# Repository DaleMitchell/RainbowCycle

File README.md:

# RainbowCycle
My very first circuit board. I'm very proud to say that the first fabrication of it worked! :)

The PCB was fabricated by Seeedstudio: http://www.seeedstudio.com/service/

Components on the board were hand soldered by me.

## YouTube Video

## Bill of materials
* 10x Common Anode RGB LEDs - 5mm Square (Sometimes called 'Super flux' or 'Piranha') 
* 1x ATMega328P-PU - same chip used by the Arduino Uno
* 2x TLC5940s - 16 Channel LED Driver
* 2x 10K Ohm Potentiometers - adjustable speed and brightness
* 2x 2K Ohm Resistors - current limiting for LED drivers
* 2x 10K Ohm Resistors - pull-up resistors for the ICs
* 1x 100uF Capacitor - filtering capacitor for stable power to ICs
* 3x 0.1uF Capacitors - also filtering capacitors for each IC
* 1x 16MHz Crystal - clock input for ATMega328P-PU
* 2x 22pF Capacitors - used by the 16MHz crystal
* 1x Mini-USB Connector - for power only, doesn't program Arduino
* 1x ISP Header - for programming the ATMega328P-PU
* 1x Terminal Blocks 5.08mm - alternative connector for power
* 1x Diode - protection against reverse polarity on block terminal

## Things I'd do differently if I wanted to revise the board

* Use trimpots that are flush with the board instead of panel mount potentiometers. Even when soldered on both sides of the board, the currently used potentiometers bend easily.
* Replace ATMega328P-PU with a microcontroller that can be programmed directly through USB. ICSP was a hassle, and I couldn't find a through-hole means of converting USB to serial.
* Provide overvoltage protection, or at least put a warning on the silkscreen that the circuit is only rated for 5V.
* Make pads on some components slightly bigger for some components, like resistors and small capacitors.
* Use slightly higher clearance for ground plane (maybe?).

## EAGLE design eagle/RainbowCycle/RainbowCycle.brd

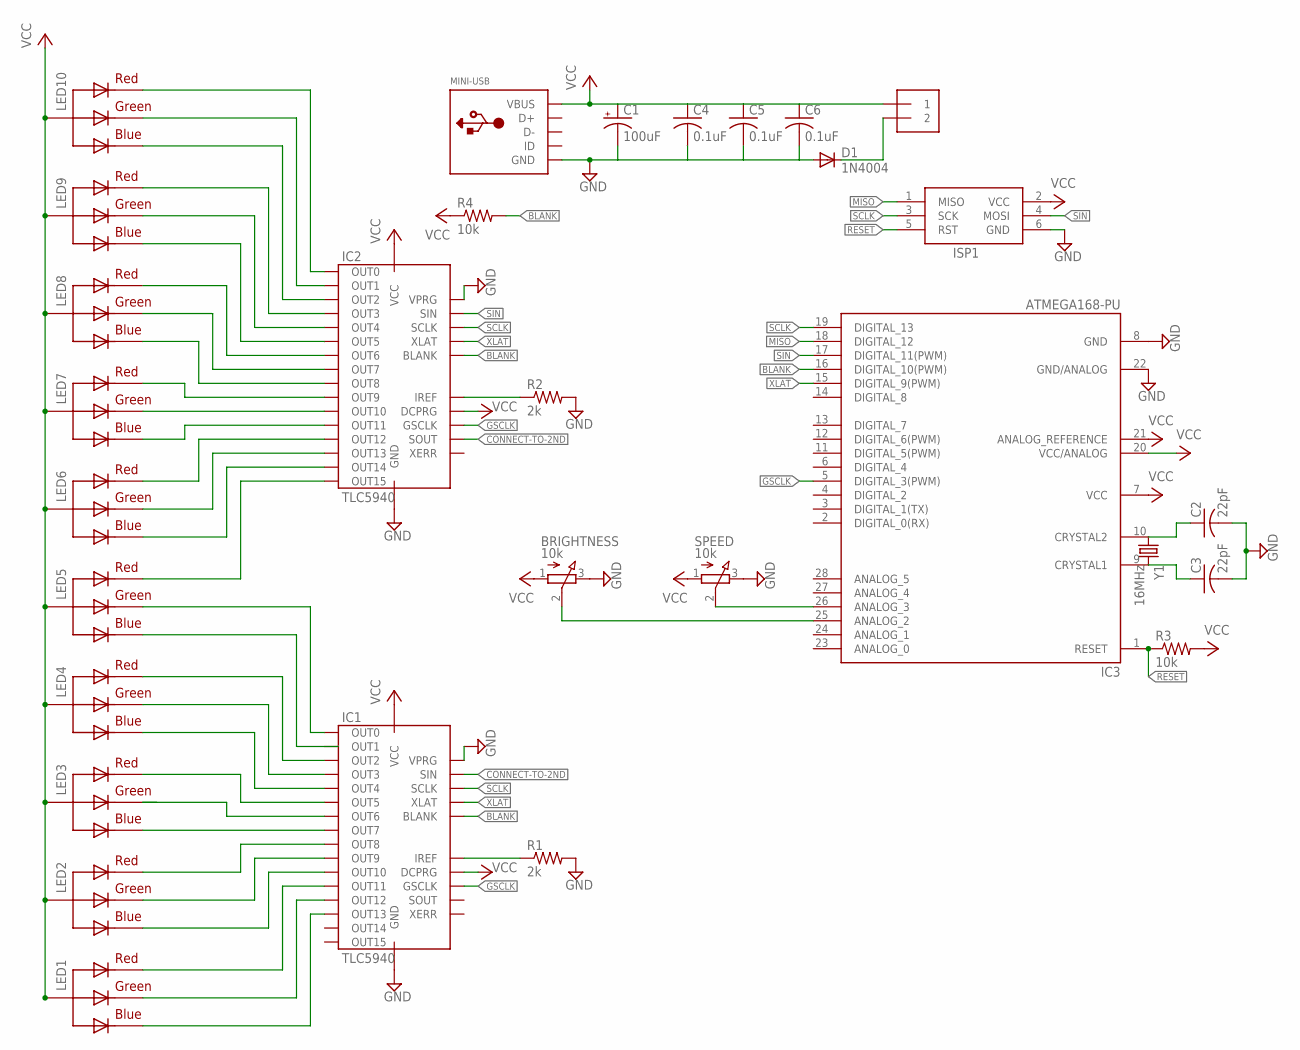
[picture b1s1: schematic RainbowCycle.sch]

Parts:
BLOCK-TERMINAL: 1X2-5.08MM
BRIGHTNESS: 10k; 3RP/1610N
C1: 100uF; E2,5-6
C2, C3: 22pF; C050-025X075
C4, C5, C6: 0.1uF; C050-025X075
D1: 1N4004; DO41-10
IC1, IC2: TLC5940; IC-PACKAGE_DIL28-3
IC3: ATMEGA168-PU; DIL28-3
ISP1: AVRISP-6; AVRISP
LED1, LED2, LED3, LED4, LED5, LED6, LED7, LED8, LED9, LED10: RGBLED_CA; PIRANHA5MM
MINI-USB: USBMOLEX; USB-MINIB-THM-MOLEX
R1, R2: 2k; 0207/10
R3, R4: 10k; 0207/10
SPEED: 10k; 3RP/1610N
Y1: 16MHz; HC49US

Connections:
BLANK: IC1.23 (BLANK), IC2.23 (BLANK), IC3.16 (DIGITAL_10(PWM)), R4.2
CONNECT-TO-2ND: IC1.26 (SIN), IC2.17 (SOUT)
GND: BRIGHTNESS.3 (E), C1.-, C2.2, C3.2, C4.2, C5.2, C6.2, D1.A, IC1.22 (GND), IC1.27 (VPRG), IC2.22 (GND), IC2.27 (VPRG), IC3.8 (GND), IC3.22 (GND/ANALOG), ISP1.6 (GND), MINI-USB.GND, MINI-USB.GND1 (GND), MINI-USB.GND4 (GND), R1.2, R2.2, SPEED.3 (E)
GSCLK: IC1.18 (GSCLK), IC2.18 (GSCLK), IC3.5 (DIGITAL_3(PWM))
MISO: IC3.18 (DIGITAL_12), ISP1.1 (MISO)
unnamed: BRIGHTNESS.2 (S), IC3.25 (ANALOG_2)
unnamed: IC3.26 (ANALOG_3), SPEED.2 (S)
unnamed: IC2.20 (IREF), R2.1
unnamed: BLOCK-TERMINAL.2, D1.C
unnamed: C3.1, IC3.9 (CRYSTAL1), Y1.2
unnamed: C2.1, IC3.10 (CRYSTAL2), Y1.1
unnamed: IC2.28 (OUT0), LED10.3 (RED)
unnamed: IC1.1 (OUT1), LED5.1 (BLUE)
unnamed: IC2.1 (OUT1), LED10.2 (GREEN)
unnamed: IC2.2 (OUT2), LED10.1 (BLUE)
unnamed: IC1.20 (IREF), R1.1
unnamed: IC2.3 (OUT3), LED9.3 (RED)
unnamed: IC2.4 (OUT4), LED9.2 (GREEN)
unnamed: IC2.5 (OUT5), LED9.1 (BLUE)
unnamed: IC2.6 (OUT6), LED8.3 (RED)
unnamed: IC2.7 (OUT7), LED8.2 (GREEN)
unnamed: IC2.8 (OUT8), LED8.1 (BLUE)
unnamed: IC2.9 (OUT9), LED7.3 (RED)
unnamed: IC2.10 (OUT10), LED7.2 (GREEN)
unnamed: IC2.11 (OUT11), LED7.1 (BLUE)
unnamed: IC2.12 (OUT12), LED6.3 (RED)
unnamed: IC2.13 (OUT13), LED6.2 (GREEN)
unnamed: IC2.14 (OUT14), LED6.1 (BLUE)
unnamed: IC2.15 (OUT15), LED5.3 (RED)
unnamed: IC1.28 (OUT0), LED5.2 (GREEN)
unnamed: IC1.13 (OUT13), LED1.1 (BLUE)
unnamed: IC1.2 (OUT2), LED4.3 (RED)
unnamed: IC1.3 (OUT3), LED4.2 (GREEN)
unnamed: IC1.4 (OUT4), LED4.1 (BLUE)
unnamed: IC1.5 (OUT5), LED3.3 (RED)
unnamed: IC1.6 (OUT6), LED3.2 (GREEN)
unnamed: IC1.7 (OUT7), LED3.1 (BLUE)
unnamed: IC1.12 (OUT12), LED1.2 (GREEN)
unnamed: IC1.11 (OUT11), LED1.3 (RED)
unnamed: IC1.10 (OUT10), LED2.1 (BLUE)
unnamed: IC1.9 (OUT9), LED2.2 (GREEN)
unnamed: IC1.8 (OUT8), LED2.3 (RED)
RESET: IC3.1 (RESET), ISP1.5 (RST), R3.1
SCLK: IC1.25 (SCLK), IC2.25 (SCLK), IC3.19 (DIGITAL_13), ISP1.3 (SCK)
SIN: IC2.26 (SIN), IC3.17 (DIGITAL_11(PWM)), ISP1.4 (MOSI)
VCC: BLOCK-TERMINAL.1, BRIGHTNESS.1 (A), C1.+, C4.1, C5.1, C6.1, IC1.19 (DCPRG), IC1.21 (VCC), IC2.19 (DCPRG), IC2.21 (VCC), IC3.7 (VCC), IC3.20 (VCC/ANALOG), IC3.21 (ANALOG_REFERENCE), ISP1.2 (VCC), LED1.4 (VCC), LED2.4 (VCC), LED3.4 (VCC), LED4.4 (VCC), LED5.4 (VCC), LED6.4 (VCC), LED7.4 (VCC), LED8.4 (VCC), LED9.4 (VCC), LED10.4 (VCC), MINI-USB.VBUS, R3.2, R4.1, SPEED.1 (A)
XLAT: IC1.24 (XLAT), IC2.24 (XLAT), IC3.15 (DIGITAL_9(PWM))

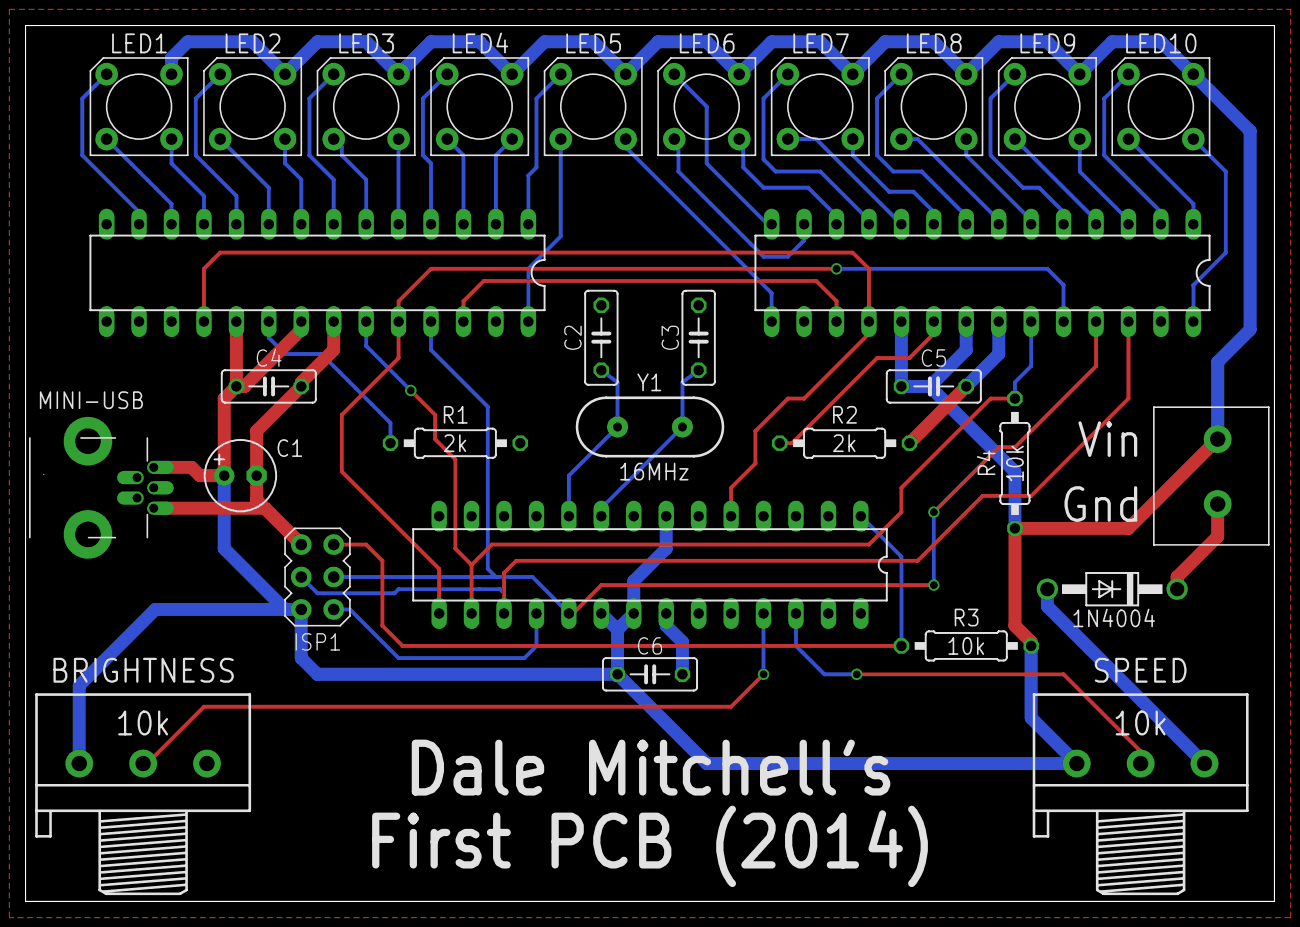
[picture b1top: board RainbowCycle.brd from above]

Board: 4 copper layers, 97.8 x 68.6 mm, 30 parts (0 on the bottom side), 47 nets.

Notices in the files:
parts and their libraries:
SparkFun-FreqCtrl: Licensing: Creative Commons ShareAlike 4.0 International - https://creativecommons.org/licenses/by-sa/4.0
